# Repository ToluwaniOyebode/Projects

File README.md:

# Projects

## Data, AI and ML portfolio

[Explore three end-to-end ML projects →](ML-Projects/README.md)

| Project | Focus |
| --- | --- |
| [Churn Intelligence](ML-Projects/churn-intelligence/) | Model comparison, calibration and a profit-based retention decision |
| [Demand Forecasting Lab](ML-Projects/demand-forecasting-lab/) | Leakage-safe rolling backtests, promotions and prediction intervals |
| [Ticket Triage NLP](ML-Projects/ticket-triage-nlp/) | Unseen-phrasing evaluation, confidence routing and similar-ticket search |

Each project reproduces from one command, ships its real results and figures, and states its own limitations. Data is synthetic and generated locally.

## Software engineering portfolio

[Explore six complete local applications →](Portfolio-Projects/README.md)

| Project                                      | Focus                                                            |
| -------------------------------------------- | ---------------------------------------------------------------- |
| [Applyboard](Portfolio-Projects/applyboard/) | Job application pipeline, versioned edits and follow-ups         |
| [LedgerLens](Portfolio-Projects/ledgerlens/) | Exact-money expense analytics, budgets and validated CSV imports |
| [Stockroom](Portfolio-Projects/stockroom/)   | Transactional inventory, idempotent reservations and fulfillment |
| [SignalDesk](Portfolio-Projects/signaldesk/) | Local document search with explainable BM25 ranking              |
| [Pitchside](Portfolio-Projects/pitchside/)   | Football event analytics, passing networks and shot maps         |
| [QueueCraft](Portfolio-Projects/queuecraft/) | Persistent background jobs, retries and crash-safe leases        |

Each project includes a working UI, demo data, an API guide, tests and local setup instructions. The collection has 45 domain tests plus HTTP and optional browser acceptance checks. [Validation evidence](Portfolio-Projects/VALIDATION.md) · [Demo and interview guide](Portfolio-Projects/INTERVIEW_GUIDE.md)

## Other projects

- [Project R.O.D.R.I.](Project-R.O.D.R.I./) — ongoing football analysis work.
- [ESP32](ESP32/) · [NodeMCU](NODEMCU/) · [Raspberry Pi](RASPBERRY/) — hardware and embedded projects.
- Stock-market notebooks and datasets in the repository root.

New portfolio applications use fictional/synthetic sample data and were built with AI assistance. Existing work remains separate from the new collection.

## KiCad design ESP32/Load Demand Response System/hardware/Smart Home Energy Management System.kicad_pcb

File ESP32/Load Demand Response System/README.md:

# Load Demand Response System
Generated using KiCad Industrial Setup Script

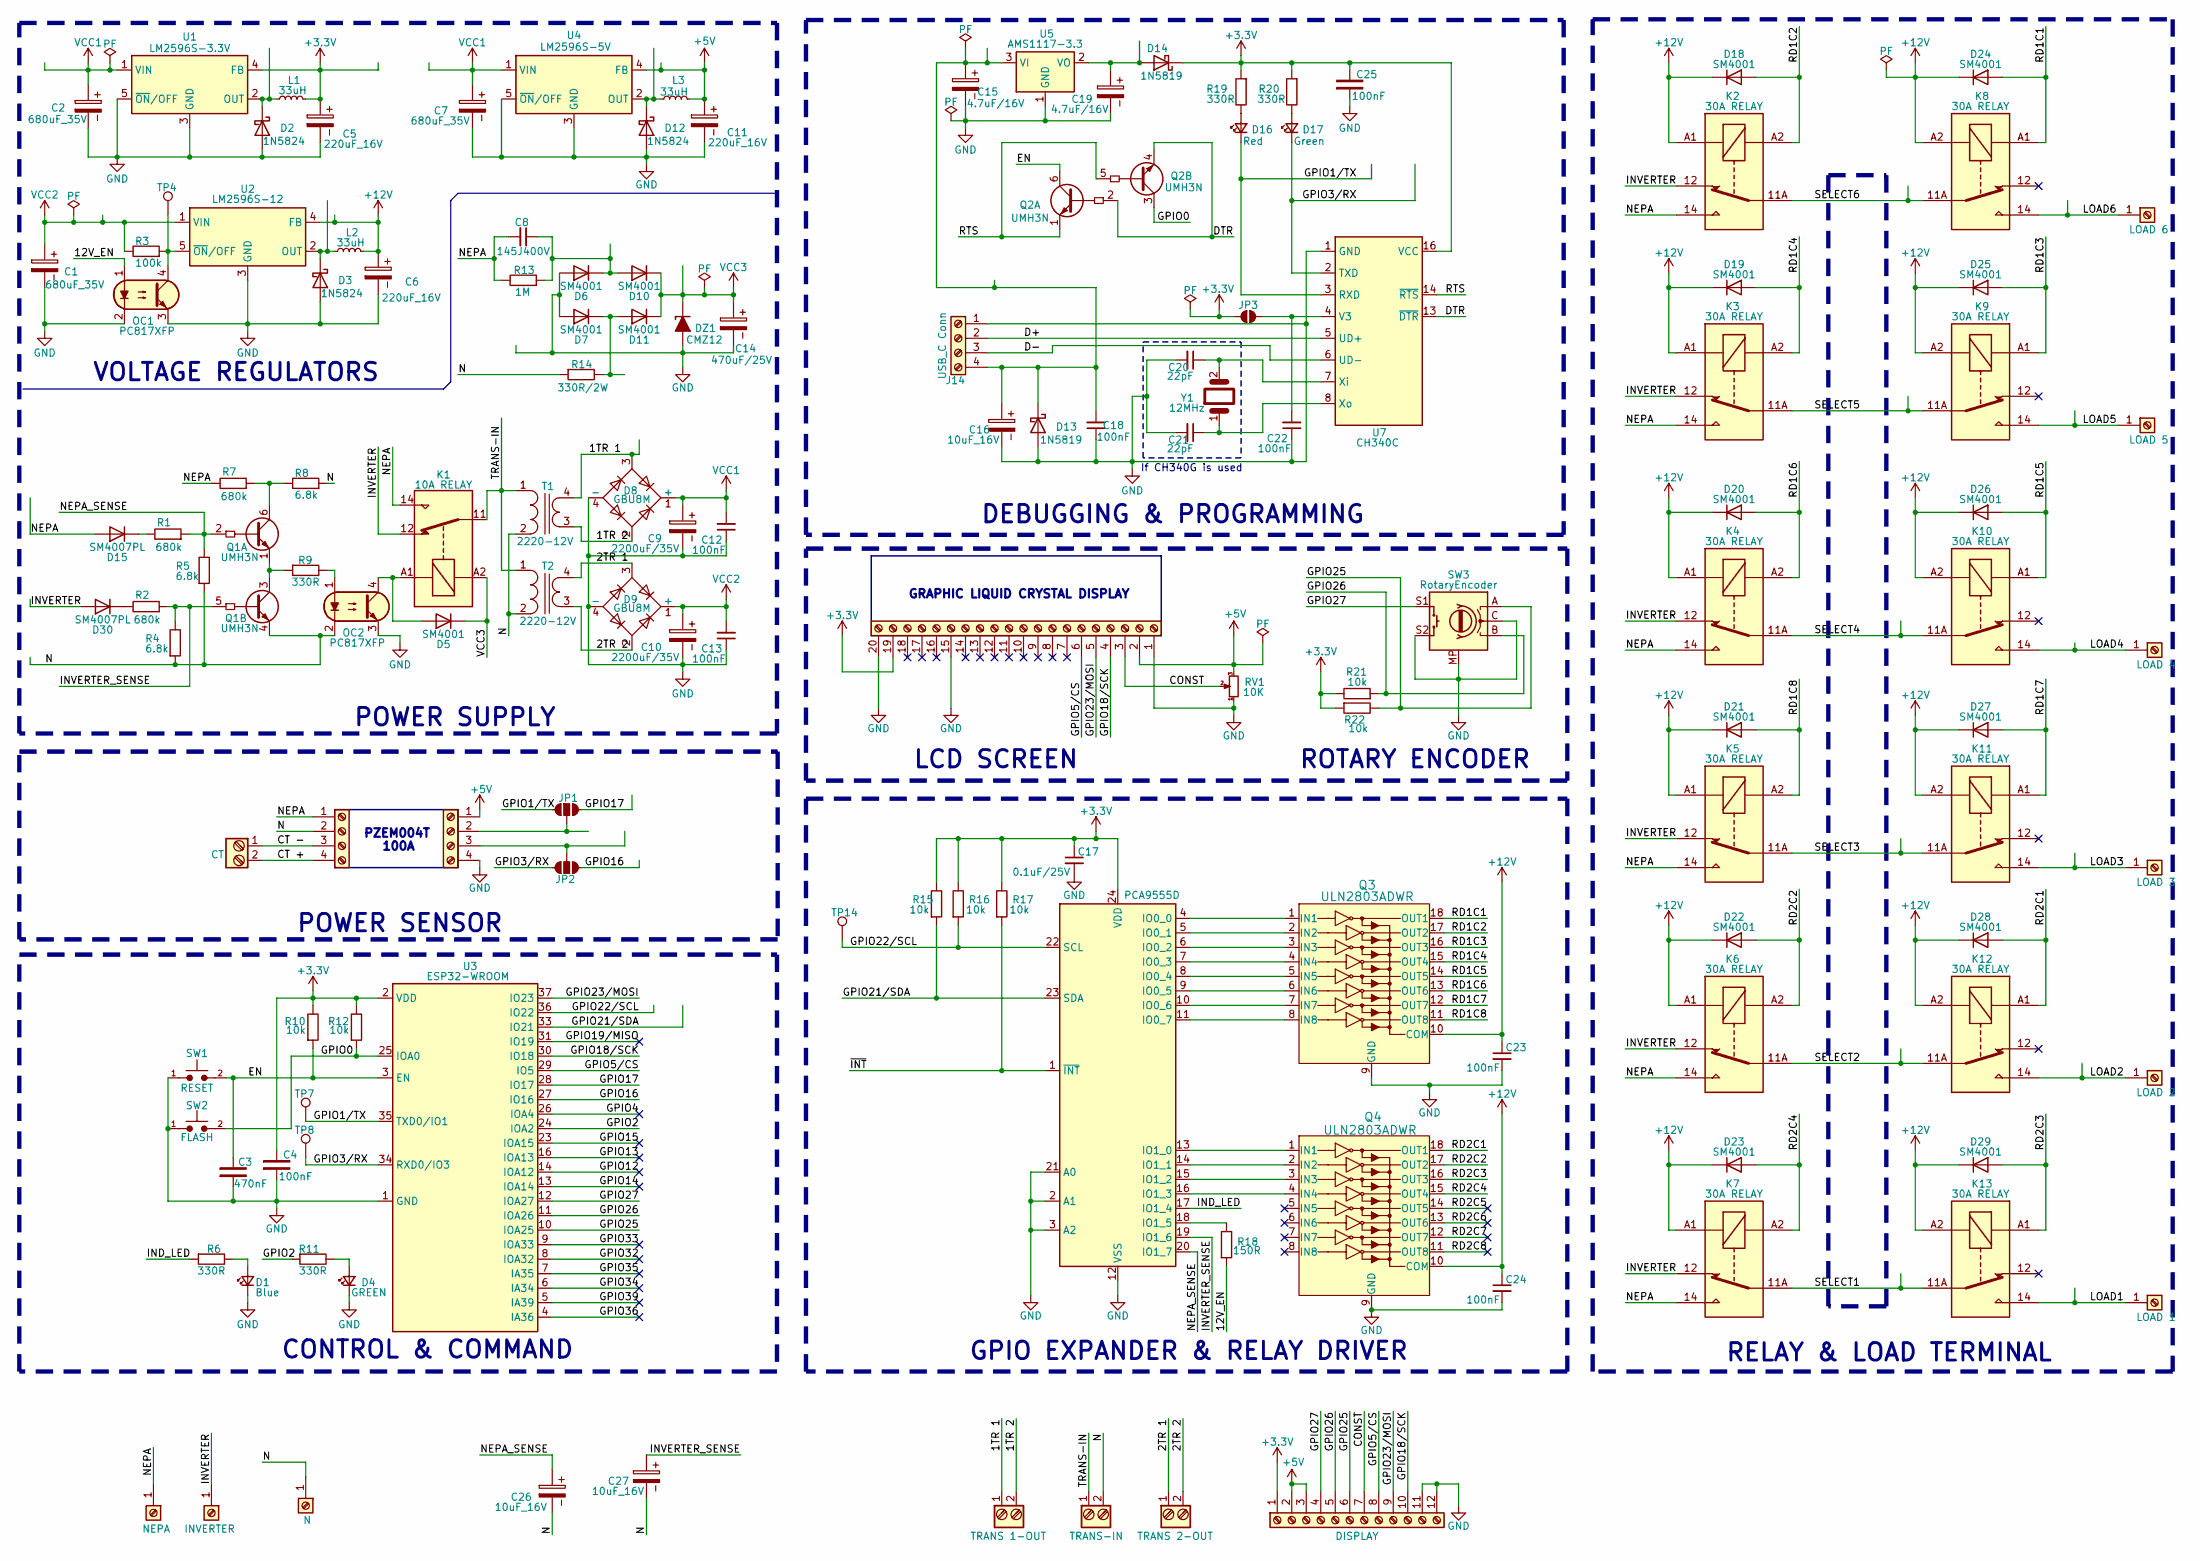
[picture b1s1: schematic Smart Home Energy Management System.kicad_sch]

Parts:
C1, C2, C7: 680uF_35V; CP_Elec_10x12.5
C3: 470nF; C_0805
C4, C12, C13, C18, C22, C25: 100nF; C_0805
C5, C6, C11: 220uF_16V; CP_Elec_6.3x7.7
C8: 145J400V; C_Rect_L19.0mm_W6.0mm_P15.00mm_MKS4
C9, C10: 2200uF/35V; CP_Radial_D18.0mm_P7.50mm
C14: 470uF/25V; CP_Elec_8x11.9
C15: 4.7uF/16V; C_CASE-B-3528-21(mm)
C16, C26, C27: 10uF_16V; C_CASE-B-3528-21(mm)
C17: 0.1uF/25V; C_0805; Voltage 25V; Tolerance 20%
C19: 4.7uF/16V; CP_EIA-3216-18_Kemet-A
C20, C21: 22pF; C_0805
C23, C24: 100nF; C_0805; Voltage 25V; Tolerance 20%
D1: Blue; LED_D3.0mm
D2, D3, D12: 1N5824; D_SMA
D4: GREEN; LED_D3.0mm
D5, D6, D7, D10, D11, D18, D19, D20, D21, D22, D23, D24, D25, D26, D27, D28, D29: SM4001; D_SMA
D8, D9: GBU8M; Diode_Bridge_Vishay_GBU
D13, D14: 1N5819; D_SMA
D15, D30: SM4007PL; D_SMA
D16: Red; LED_D3.0mm
D17: Green; LED_D3.0mm
DZ1: CMZ12; D_SOD-123
J1: NEPA; TestPoint_Plated_Hole_D5.0mm
J2: INVERTER; TestPoint_Plated_Hole_D5.0mm
J3: CT; PinHeader_1x02_P2.54mm_Vertical
J6: PZEM_LOAD; TerminalBlock_MaiXu_MX126-5.0-04P_1x04_P5.00mm
J10: N; TestPoint_Plated_Hole_D5.0mm
J11: PZEM_SIG; PinHeader_1x04_P2.54mm_Vertical
J14: USB_C Conn; PinHeader_1x04_P2.54mm_Vertical
J15: TRANS 1-OUT; TerminalBlock_Phoenix_PT-1,5-2-5.0-H_1x02_P5.00mm_Horizontal
J16: 128X64 GLCD
J17: TRANS-IN; TerminalBlock_Phoenix_PT-1,5-2-5.0-H_1x02_P5.00mm_Horizontal
J18: TRANS 2-OUT; TerminalBlock_Phoenix_PT-1,5-2-5.0-H_1x02_P5.00mm_Horizontal
J19: DISPLAY; PinHeader_1x12_P2.54mm_Vertical
J20: LOAD 6; TestPoint_Plated_Hole_D5.0mm
J21: LOAD 5; TestPoint_Plated_Hole_D5.0mm
J22: LOAD 4; TestPoint_Plated_Hole_D5.0mm
J23: LOAD 3; TestPoint_Plated_Hole_D5.0mm
J24: LOAD 2; TestPoint_Plated_Hole_D5.0mm
J25: LOAD 1; TestPoint_Plated_Hole_D5.0mm
JP1, JP2: SolderJumper-3_P1.3mm_Open_Pad1.0x1.5mm
JP3: SolderJumper-2_P1.3mm_Open_Pad1.0x1.5mm
K1: 10A RELAY; Relay_SPDT_Finder_36.11
K2, K3, K4, K5, K6, K7, K8, K9, K10, K11, K12, K13: 30A RELAY; Relay_SPDT_RAYEX-L90
L1, L2, L3: 33uH; L_12x12mm_H6mm
OC1, OC2: PC817XFP; SOP-4_4.4x2.6mm_P1.27mm
Q1, Q2: UMH3N; SOT-363_SC-70-6
Q3, Q4: ULN2803ADWR; SOIC-18_W7.5mm; MPN ULN2803ADWR; Digi-Key_PN 296-15777-1-ND
R1, R2, R7: 680k; R_0805
R3: 100k; R_0805
R4, R5, R8: 6.8k; R_0805
R6, R9, R11, R19, R20: 330R; R_0805
R10, R12, R15, R16, R17, R21, R22: 10k; R_0805
R13: 1M; R_Axial_DIN0207_L6.3mm_D2.5mm_P7.62mm_Horizontal
R14: 330R/2W; R_Axial_DIN0309_L9.0mm_D3.2mm_P20.32mm_Horizontal
R18: 150R; R_0805
RV1: 10K; Potentiometer_Bourns_3296W_Vertical
SW1: RESET; SW_TS-1088-AR02016
SW2: FLASH; SW_TS-1088-AR02016
SW3: RotaryEncoder
T1, T2: 2220-12V
TP4, TP7, TP8, TP14: TestPoint; TestPoint_Pad_D1.5mm
U1: LM2596S-3.3V; TO-263-5_L10.2-W8.9-P1.70-TL
U2: LM2596S-12; TO-263-5_L10.2-W8.9-P1.70-TL
U3: ESP32-WROOM; ESP32-WROOM-32E
U4: LM2596S-5V; TO-263-5_L10.2-W8.9-P1.70-TL
U5: AMS1117-3.3; SOT-223-3_L6.5-W3.4-P2.30-LS7.0-BR
U6: PCA9555D; SOIC-24W_7.5x15.4mm_P1.27mm
U7: CH340C; SOIC-16_3.9x9.9mm_P1.27mm
Y1: 12MHz; CRYSTAL-SMD_L11.5-W4.8-LS12.7

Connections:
+3.3V: C4.2, C5.1, C17.1, C25.2, D14.1 (K), J16.19, J19.1, JP3.2 (B), L1.2, R10.2, R12.2, R15.2, R16.2, R17.2, R19.1, R20.1, R21.2, R22.1, U1.4 (FB), U3.2 (VDD), U6.24 (VDD), U7.16 (VCC)
+5V: C11.1, J11.1, J16.2, J19.2, J19.3, L3.2, RV1.3, U4.4 (FB)
+12V: C6.1, C23.1, C24.1, D18.1 (K), D19.1 (K), D20.1 (K), D21.1 (K), D22.1 (K), D23.1 (K), D24.1 (K), D25.1 (K), D26.1 (K), D27.1 (K), D28.1 (K), D29.1 (K), K2.A1, K3.A1, K4.A1, K5.A1, K6.A1, K7.A1, K8.A2, K9.A2, K10.A2, K11.A2, K12.A2, K13.A2, L2.2, Q3.10 (COM), Q4.10 (COM), U2.4 (FB)
/1TR 1: D8.3, J15.1, T1.4 (SB)
/1TR 2: D8.2, J15.2, T1.3 (SA)
/2TR 1: D9.3, J18.1, T2.4 (SB)
/2TR 2: D9.2, J18.2, T2.3 (SA)
/12V_EN: OC1.1, R18.1
/CONST: J16.3, J19.7, RV1.2
/CT +: J3.2, J6.4
/CT -: J3.1, J6.3
/D+: J14.2, U7.5 (UD+)
/D-: J14.3, U7.6 (UD-)
/DTR: Q2.2 (B1), Q2.4 (E2), U7.13 (~DTR)
/EN: C3.2, Q2.6 (C1), R10.1, SW1.2, U3.3 (EN)
/GPIO0: Q2.3 (C2), R12.1, SW2.2, U3.25 (IOA0)
/GPIO1/TX: D16.1 (K), JP1.1 (A), TP7.1, U3.35 (TXD0/IO1), U7.3 (RXD)
/GPIO2: R11.1, U3.24 (IOA2)
/GPIO3/RX: D17.1 (K), JP2.3 (C), TP8.1, U3.34 (RXD0/IO3), U7.2 (TXD)
/GPIO4: U3.26 (IOA4)
/GPIO5/CS: J16.6, J19.8, U3.29 (IO5)
/GPIO12: U3.14 (IOA12)
/GPIO13: U3.16 (IOA13)
/GPIO14: U3.13 (IOA14)
/GPIO15: U3.23 (IOA15)
/GPIO16: JP2.1 (A), U3.27 (IO16)
/GPIO17: JP1.3 (C), U3.28 (IO17)
/GPIO18/SCK: J16.4, J19.10, U3.30 (IO18)
/GPIO19/MISO: U3.31 (IO19)
/GPIO21/SDA: R15.1, U3.33 (IO21), U6.23 (SDA)
/GPIO22/SCL: R16.1, TP14.1, U3.36 (IO22), U6.22 (SCL)
/GPIO23/MOSI: J16.5, J19.9, U3.37 (IO23)
/GPIO25: J19.6, R22.2, SW3.A, U3.10 (IOA25)
/GPIO26: J19.5, R21.1, SW3.B, U3.11 (IOA26)
/GPIO27: J19.4, SW3.S1, U3.12 (IOA27)
/GPIO32: U3.8 (IOA32)
/GPIO33: U3.9 (IOA33)
/GPIO34: U3.6 (IA34)
/GPIO35: U3.7 (IA35)
/GPIO36: U3.4 (IA36)
/GPIO39: U3.5 (IA39)
/IND_LED: R6.1, U6.17 (IO1_4)
/INVERTER: D30.2 (A), J2.1, K1.12, K2.12, K3.12, K4.12, K5.12, K6.12, K7.12
/INVERTER_SENSE: C27.1, Q1.5 (B2), R2.1, R4.2, U6.19 (IO1_6)
/LOAD1: J25.1, K13.14
/LOAD2: J24.1, K12.14
/LOAD3: J23.1, K11.14
/LOAD4: J22.1, K10.14
/LOAD5: J21.1, K9.14
/LOAD6: J20.1, K8.14
/N: C26.2, C27.2, J6.2, J10.1, J17.2, OC2.2, Q1.4 (E2), R4.1, R5.1, R8.1, R14.1, T1.2 (AB), T2.2 (AB)
/NEPA: C8.2, D15.2 (A), J1.1, J6.1, K1.14, K2.14, K3.14, K4.14, K5.14, K6.14, K7.14, R7.2, R13.2
/NEPA_SENSE: C26.1, Q1.2 (B1), R1.1, R5.2, U6.20 (IO1_7)
/RD1C1: D24.2 (A), K8.A1, Q3.18 (OUT1)
/RD1C2: D18.2 (A), K2.A2, Q3.17 (OUT2)
/RD1C3: D25.2 (A), K9.A1, Q3.16 (OUT3)
/RD1C4: D19.2 (A), K3.A2, Q3.15 (OUT4)
/RD1C5: D26.2 (A), K10.A1, Q3.14 (OUT5)
/RD1C6: D20.2 (A), K4.A2, Q3.13 (OUT6)
/RD1C7: D27.2 (A), K11.A1, Q3.12 (OUT7)
/RD1C8: D21.2 (A), K5.A2, Q3.11 (OUT8)
/RD2C1: D28.2 (A), K12.A1, Q4.18 (OUT1)
/RD2C2: D22.2 (A), K6.A2, Q4.17 (OUT2)
/RD2C3: D29.2 (A), K13.A1, Q4.16 (OUT3)
/RD2C4: D23.2 (A), K7.A2, Q4.15 (OUT4)
/RD2C5: Q4.14 (OUT5)
/RD2C6: Q4.13 (OUT6)
/RD2C7: Q4.12 (OUT7)
/RD2C8: Q4.11 (OUT8)
/RTS: Q2.1 (E1), Q2.5 (B2), U7.14 (~RTS)
/SELECT1: K7.11A, K7.11B, K13.11A, K13.11B
/SELECT2: K6.11A, K6.11B, K12.11A, K12.11B
/SELECT3: K5.11A, K5.11B, K11.11A, K11.11B
/SELECT4: K4.11A, K4.11B, K10.11A, K10.11B
/SELECT5: K3.11A, K3.11B, K9.11A, K9.11B
/SELECT6: K2.11A, K2.11B, K8.11A, K8.11B
/TRANS-IN: J17.1, K1.11, T1.1 (AA), T2.1 (AA)
/~INT: R17.1, U6.1 (~INT)
GND: C1.2, C2.2, C3.1, C4.1, C5.2, C6.2, C7.2, C9.2, C10.2, C11.2, C12.1, C13.1, C14.2, C15.2, C16.2, C17.2, C18.1, C19.2, C20.2, C21.2, C22.1, C23.2, C24.2, C25.1, D1.1 (K), D2.2 (A), D3.2 (A), D4.1 (K), D6.2 (A), D7.2 (A), D8.4 (-), D9.4 (-), D12.2 (A), D13.2 (A), DZ1.2 (A), J11.4, J14.1, J16.1, J16.15, J16.20, J19.11, J19.12, OC1.2, OC1.3, OC2.3, Q3.9 (GND), Q4.9 (GND), RV1.1, SW1.1, SW2.1, SW3.C, SW3.MP, SW3.S2, U1.3 (GND), U1.5 (~ON/OFF), U1.6 (GND), U2.3 (GND), U2.6 (GND), U3.1 (GND), U3.15 (GND), U3.38 (GND), U3.39 (GND), U4.3 (GND), U4.5 (~ON/OFF), U4.6 (GND), U5.1 (GND), U6.2 (A1), U6.3 (A2), U6.12 (VSS), U6.21 (A0), U7.1 (GND)
unnamed: D1.2 (A), R6.2
unnamed: D2.1 (K), L1.1, U1.2 (OUT)
unnamed: D3.1 (K), L2.1, U2.2 (OUT)
unnamed: D4.2 (A), R11.2
unnamed: D5.2 (A), K1.A1, OC2.4
unnamed: C8.1, D6.1 (K), D10.2 (A), R13.1
unnamed: D7.1 (K), D11.2 (A), R14.2
unnamed: D12.1 (K), L3.1, U4.2 (OUT)
unnamed: C15.1, C16.1, C18.2, D13.1 (K), J14.4, U5.3 (VI)
unnamed: C19.1, D14.2 (A), U5.2 (VO), U5.4 (VO)
unnamed: D15.1 (K), R1.2
unnamed: D16.2 (A), R19.2
unnamed: D17.2 (A), R20.2
unnamed: D30.1 (K), R2.2
unnamed: J11.2, JP1.2 (B)
unnamed: J11.3, JP2.2 (B)
unnamed: C22.2, JP3.1 (A), U7.4 (V3)
unnamed: OC2.1, R9.2
unnamed: Q1.6 (C1), R7.1, R8.2
unnamed: Q1.1 (E1), Q1.3 (C2), R9.1
unnamed: Q3.1 (IN1), U6.4 (IO0_0)
unnamed: Q3.2 (IN2), U6.5 (IO0_1)
unnamed: Q3.3 (IN3), U6.6 (IO0_2)
unnamed: Q3.4 (IN4), U6.7 (IO0_3)
unnamed: Q3.5 (IN5), U6.8 (IO0_4)
unnamed: Q3.6 (IN6), U6.9 (IO0_5)
unnamed: Q3.7 (IN7), U6.10 (IO0_6)
unnamed: Q3.8 (IN8), U6.11 (IO0_7)
unnamed: Q4.1 (IN1), U6.13 (IO1_0)
unnamed: Q4.2 (IN2), U6.14 (IO1_1)
unnamed: Q4.3 (IN3), U6.15 (IO1_2)
unnamed: Q4.4 (IN4), U6.16 (IO1_3)
unnamed: OC1.4, R3.1, TP4.1, U2.5 (~ON/OFF)
unnamed: R18.2, U6.18 (IO1_5)
unnamed: C20.1, U7.7 (Xi), Y1.2
unnamed: C21.1, U7.8 (Xo), Y1.1
VCC1: C2.1, C7.1, C9.1, C12.2, D8.1 (+), U1.1 (VIN), U4.1 (VIN)
VCC2: C1.1, C10.1, C13.2, D9.1 (+), R3.2, U2.1 (VIN)
VCC3: C14.1, D5.1 (K), D10.1 (K), D11.1 (K), DZ1.1 (K), K1.A2

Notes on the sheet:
VOLTAGE REGULATORS
LCD SCREEN
ROTARY ENCODER
POWER SUPPLY
If CH340G is used
DEBUGGING & PROGRAMMING
POWER SENSOR
RELAY & LOAD TERMINAL
CONTROL & COMMAND
PZEM004T
GRAPHIC LIQUID CRYSTAL DISPLAY
100A
GPIO EXPANDER & RELAY DRIVER

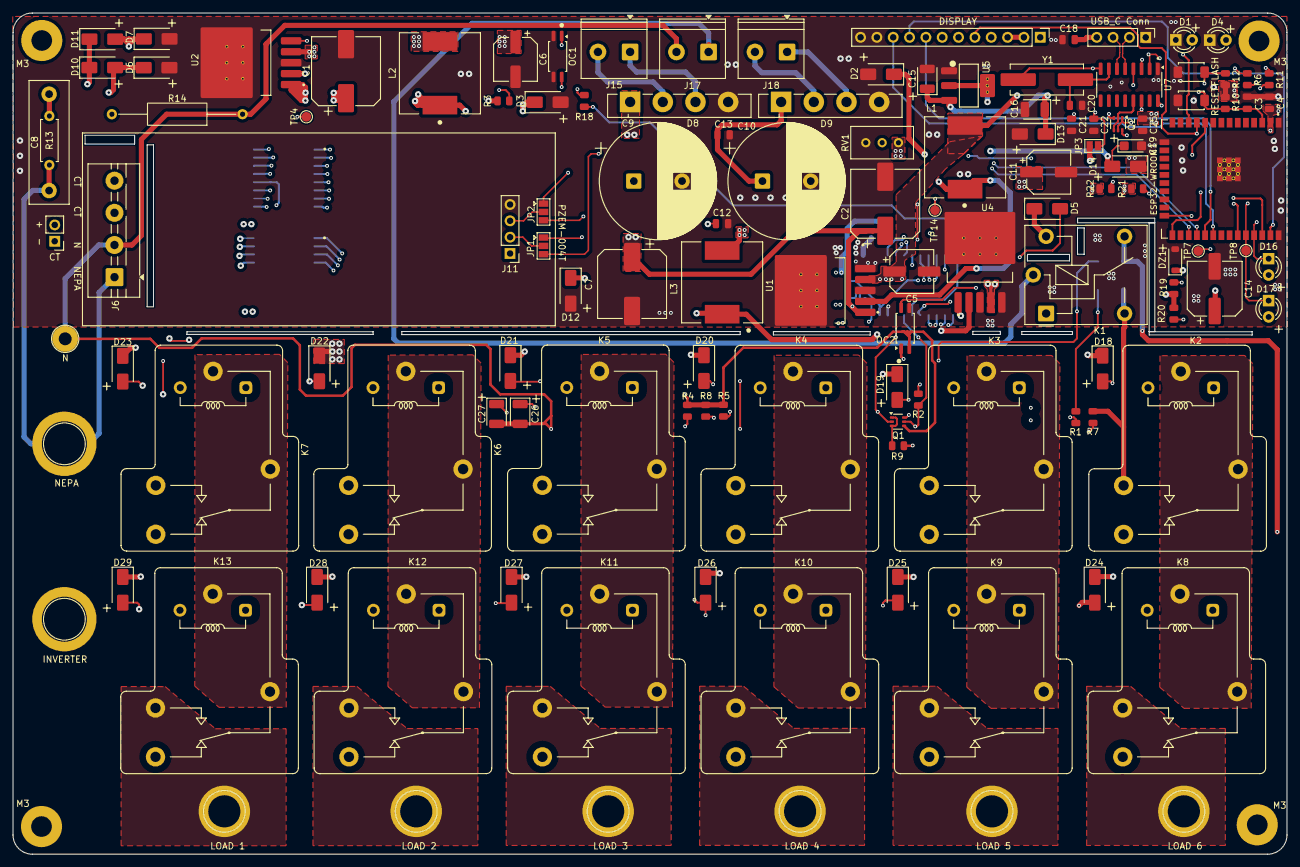
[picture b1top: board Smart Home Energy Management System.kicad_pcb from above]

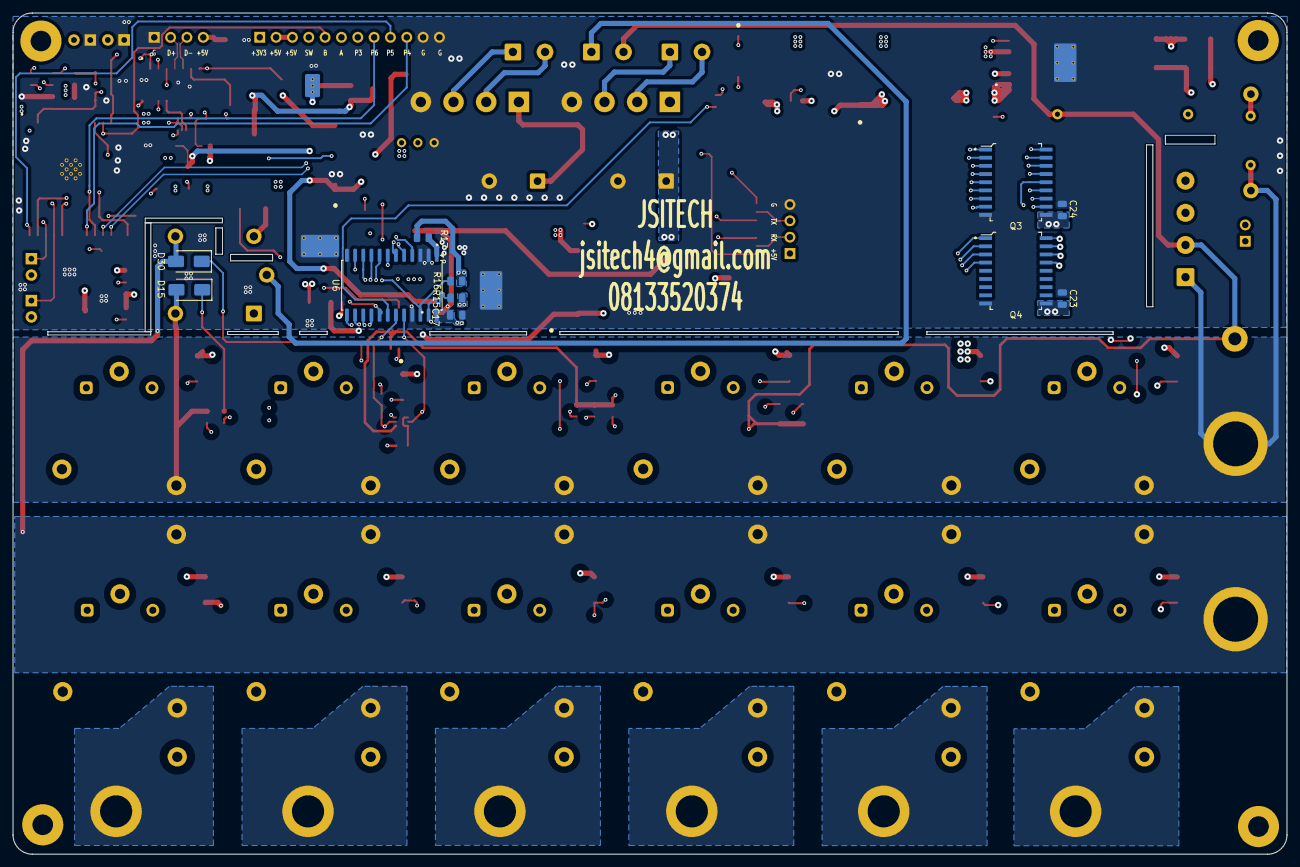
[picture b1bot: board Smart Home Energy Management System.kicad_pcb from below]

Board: 4 copper layers, 198.1 x 130.8 mm, 137 parts (11 on the bottom side), 102 nets.

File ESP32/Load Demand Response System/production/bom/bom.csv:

Designator,Footprint,Quantity,Value,LCSC Part #
"C1, C2, C7",CP_Elec_10x12.5,3,680uF_35V,
"C10, C9",CP_Radial_D18.0mm_P7.50mm,2,2200uF/35V,
"C11, C5, C6",CP_Elec_6.3x7.7,3,220uF_16V,
"C12, C13, C18, C22, C23, C24, C25, C4",C_0805,8,100nF,
C14,CP_Elec_8x11.9,1,470uF/25V,
C15,C_CASE-B-3528-21(mm),1,4.7uF/16V,
"C16, C26, C27",C_CASE-B-3528-21(mm),3,10uF_16V,
C17,C_0805,1,0.1uF/25V,
C19,CP_EIA-3216-18_Kemet-A,1,4.7uF/16V,
"C20, C21",C_0805,2,22pF,
C3,C_0805,1,470nF,
C8,C_Rect_L19.0mm_W6.0mm_P15.00mm_MKS4,1,145J400V,
D1,LED_D3.0mm,1,Blue,
"D10, D11, D18, D19, D20, D21, D22, D23, D24, D25, D26, D27, D28, D29, D5, D6, D7",D_SMA,17,SM4001,
"D12, D2, D3",D_SMA,3,1N5824,
"D13, D14",D_SMA,2,1N5819,
"D15, D30",D_SMA,2,SM4007PL,
D16,LED_D3.0mm,1,Red,
"D17, D4",LED_D3.0mm,2,Green,
"D8, D9",Diode_Bridge_Vishay_GBU,2,GBU8M,
DZ1,D_SOD-123,1,CMZ12,
J1,TestPoint_Plated_Hole_D5.0mm,1,NEPA,
J10,TestPoint_Plated_Hole_D5.0mm,1,N,
J11,PinHeader_1x04_P2.54mm_Vertical,1,PZEM_SIG,
J14,PinHeader_1x04_P2.54mm_Vertical,1,USB_C Conn,
J15,"TerminalBlock_Phoenix_PT-1,5-2-5.0-H_1x02_P5.00mm_Horizontal",1,TRANS 1-OUT,
J17,"TerminalBlock_Phoenix_PT-1,5-2-5.0-H_1x02_P5.00mm_Horizontal",1,TRANS-IN,
J18,"TerminalBlock_Phoenix_PT-1,5-2-5.0-H_1x02_P5.00mm_Horizontal",1,TRANS 2-OUT,
J19,PinHeader_1x12_P2.54mm_Vertical,1,DISPLAY,
J2,TestPoint_Plated_Hole_D5.0mm,1,INVERTER,
J20,TestPoint_Plated_Hole_D5.0mm,1,LOAD 6,
J21,TestPoint_Plated_Hole_D5.0mm,1,LOAD 5,
J22,TestPoint_Plated_Hole_D5.0mm,1,LOAD 4,
J23,TestPoint_Plated_Hole_D5.0mm,1,LOAD 3,
J24,TestPoint_Plated_Hole_D5.0mm,1,LOAD 2,
J25,TestPoint_Plated_Hole_D5.0mm,1,LOAD 1,
J3,PinHeader_1x02_P2.54mm_Vertical,1,CT,
J6,TerminalBlock_MaiXu_MX126-5.0-04P_1x04_P5.00mm,1,PZEM_LOAD,
"JP1, JP2",SolderJumper-3_P1.3mm_Open_Pad1.0x1.5mm,2,~,
JP3,SolderJumper-2_P1.3mm_Open_Pad1.0x1.5mm,1,~,
K1,Relay_SPDT_Finder_36.11,1,10A RELAY,
"K10, K11, K12, K13, K2, K3, K4, K5, K6, K7, K8, K9",Relay_SPDT_RAYEX-L90,12,30A RELAY,
"L1, L2, L3",L_12x12mm_H6mm,3,33uH,
"OC1, OC2",SOP-4_4.4x2.6mm_P1.27mm,2,PC817XFP,
"Q1, Q2",SOT-363_SC-70-6,2,UMH3N,
"Q3, Q4",SOIC-18_W7.5mm,2,ULN2803ADWR,ULN2803ADWR
"R1, R2, R7",R_0805,3,680k,
"R10, R12, R15, R16, R17, R21, R22",R_0805,7,10k,
"R11, R19, R20, R6, R9",R_0805,5,330R,
R13,R_Axial_DIN0207_L6.3mm_D2.5mm_P7.62mm_Horizontal,1,1M,
R14,R_Axial_DIN0309_L9.0mm_D3.2mm_P20.32mm_Horizontal,1,330R/2W,
R18,R_0805,1,150R,
R3,R_0805,1,100k,
"R4, R5, R8",R_0805,3,6.8k,
RV1,Potentiometer_Bourns_3296W_Vertical,1,10K,
SW1,SW_TS-1088-AR02016,1,RESET,
SW2,SW_TS-1088-AR02016,1,FLASH,
"TP14, TP4, TP7, TP8",TestPoint_Pad_D1.5mm,4,TestPoint,
U1,TO-263-5_L10.2-W8.9-P1.70-TL,1,LM2596S-3.3V,
U2,TO-263-5_L10.2-W8.9-P1.70-TL,1,LM2596S-12,
U3,ESP32-WROOM-32E,1,ESP32-WROOM,
U4,TO-263-5_L10.2-W8.9-P1.70-TL,1,LM2596S-5V,
U5,SOT-223-3_L6.5-W3.4-P2.30-LS7.0-BR,1,AMS1117-3.3,
U6,SOIC-24W_7.5x15.4mm_P1.27mm,1,PCA9555D,
U7,SOIC-16_3.9x9.9mm_P1.27mm,1,CH340C,
Y1,CRYSTAL-SMD_L11.5-W4.8-LS12.7,1,12MHz,

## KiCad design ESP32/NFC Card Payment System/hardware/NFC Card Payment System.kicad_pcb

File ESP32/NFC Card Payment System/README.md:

# NFC Card Payment System
Generated using KiCad Industrial Setup Script

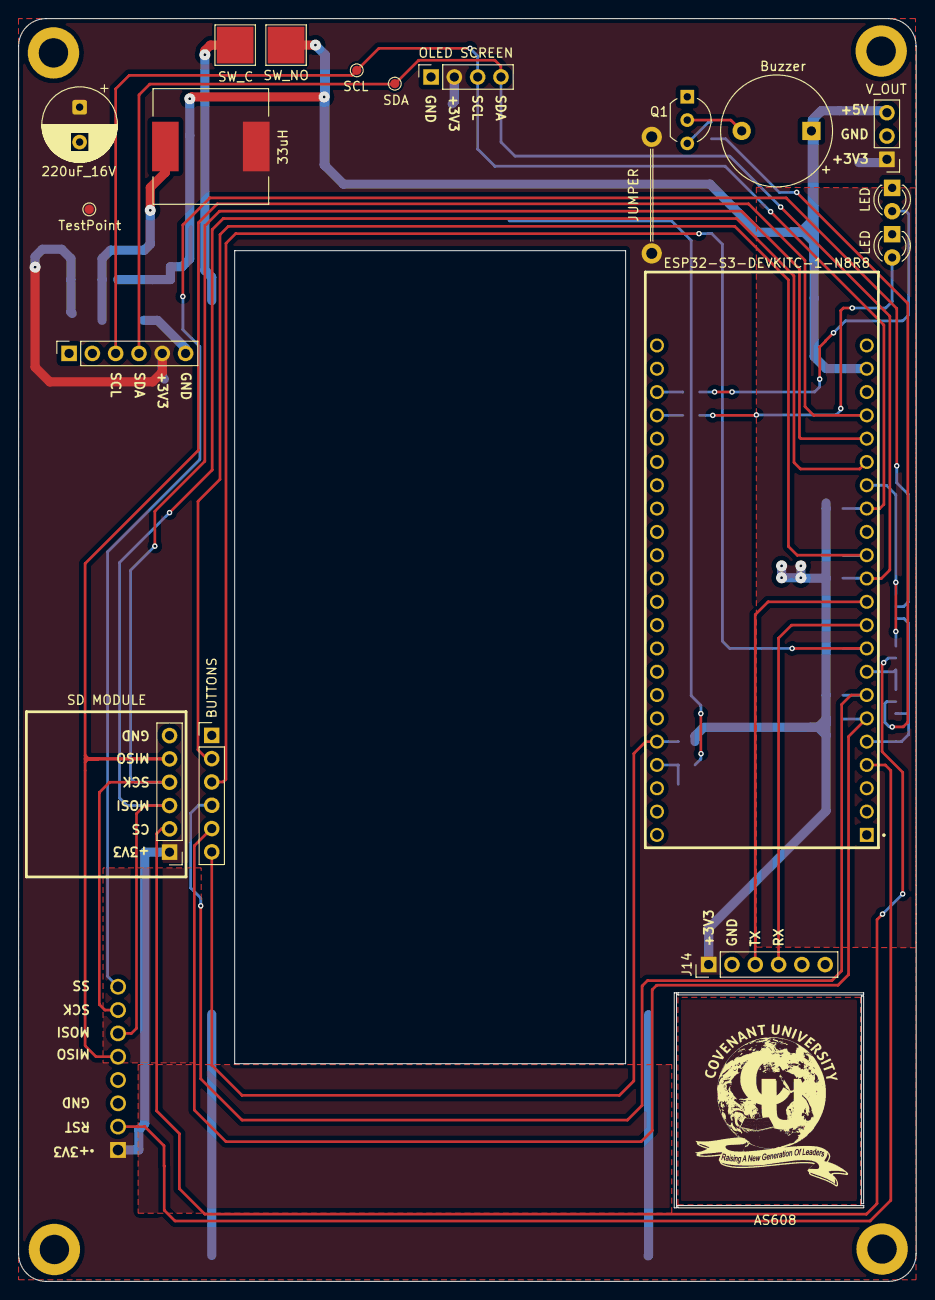
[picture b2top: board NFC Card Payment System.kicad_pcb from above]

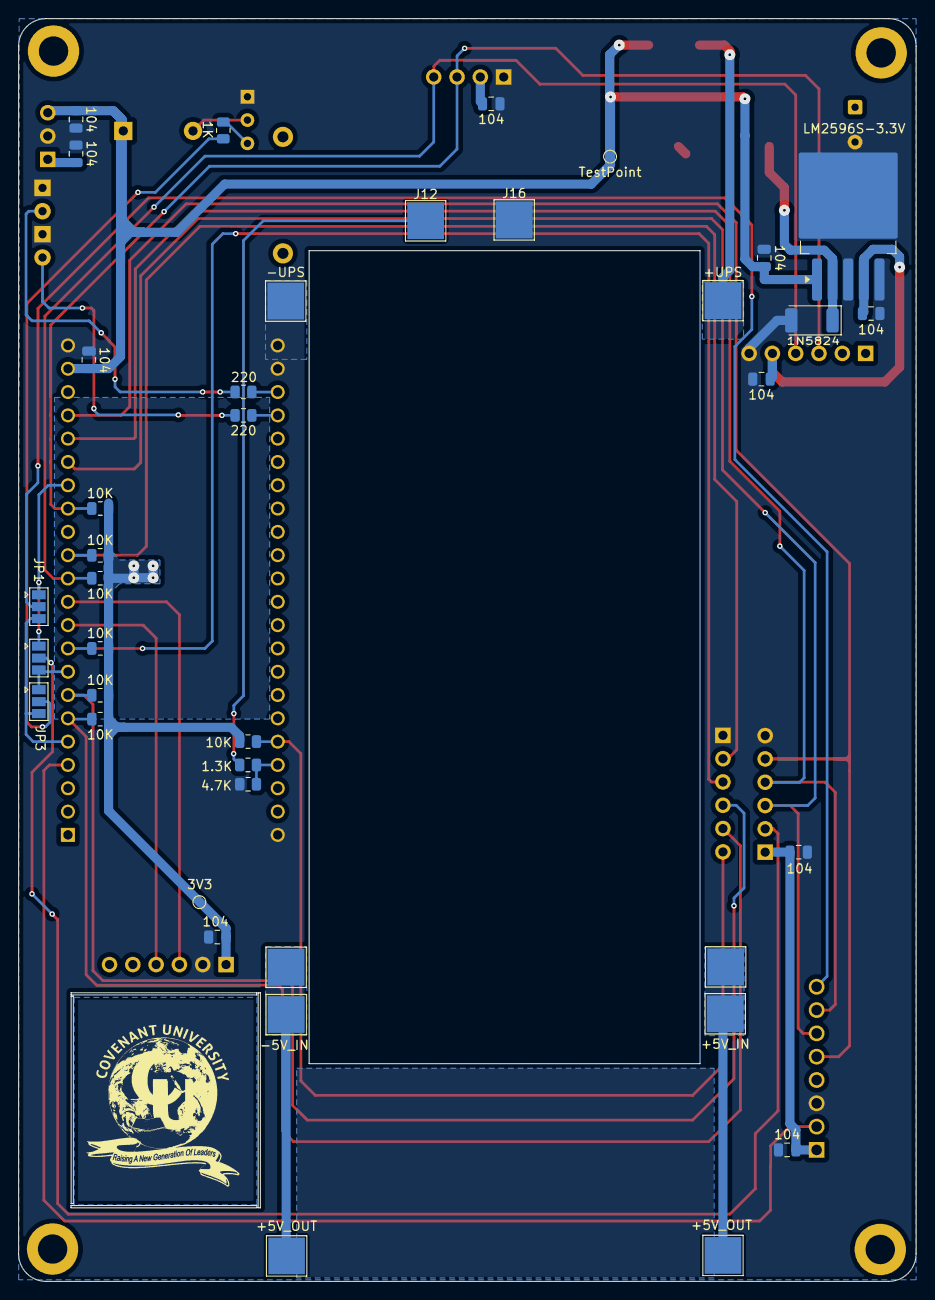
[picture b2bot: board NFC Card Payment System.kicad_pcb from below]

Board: 2 copper layers, 97.8 x 137.6 mm, 58 parts (39 on the bottom side), 34 nets.

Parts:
3.3V2: 3V3; TestPoint_Pad_D1.0mm
3.3V5, 5V1: TestPoint; TestPoint_Pad_D1.0mm
BZ1: Buzzer; Buzzer_12x9.5RM7.6
C1, C2, C3, C4, C5, C7, C8, C9, C10, C11: 104; C_0805_2012Metric
C6: 220uF_16V; CP_Radial_D8.0mm_P3.80mm
D1, D3: LED; LED_D3.0mm
D2: 1N5824; D_2010_5025Metric
J1: RTC; PinSocket_1x06_P2.54mm_Vertical
J2: OLED SCREEN; PinSocket_1x04_P2.54mm_Vertical
J3, J4: +5V_OUT; TestPoint_Pad_4.0x4.0mm
J5, J5#2: +5V_IN; TestPoint_Pad_4.0x4.0mm
J6, J6#2: -5V_IN; TestPoint_Pad_4.0x4.0mm
J9: +UPS; TestPoint_Pad_4.0x4.0mm
J10: -UPS; TestPoint_Pad_4.0x4.0mm
J11: V_OUT; PinHeader_1x03_P2.54mm_Vertical
J12: +BATT; TestPoint_Pad_4.0x4.0mm
J13: BUTTONS; PinHeader_1x06_P2.54mm_Vertical
J14: AS608; PinHeader_1x06_P2.54mm_Vertical
J15: SD MODULE; PinHeader_1x06_P2.54mm_Vertical
J16: -BATT; TestPoint_Pad_4.0x4.0mm
J17: SW_C; TestPoint_Pad_4.0x4.0mm
J18: SW_NO; TestPoint_Pad_4.0x4.0mm
JP1, JP2, JP3: SolderJumper-3_P1.3mm_Open_Pad1.0x1.5mm
L1: 33uH; L_12x12mm_H4.5mm
Q1: 2SC1815; TO-92_Inline_Wide
R1, R2, R7, R8, R9, R10, R11: 10K; R_0805_2012Metric
R3, R4: 220; R_0805_2012Metric
R5: 1.3K; R_0805_2012Metric
R6: 4.7K; R_0805_2012Metric
R12: 1K; R_0805_2012Metric
SCL1: SCL; TestPoint_Pad_D1.0mm
SDA1: SDA; TestPoint_Pad_D1.0mm
U1: ESP32-S3-DEVKITC-1-N8R8; ESP32-S3-DEVKITC
U2: LM2596S-3.3V; TO-263-5_TabPin3
U3: RC522; RC522 RFID

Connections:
+3.3V: 3.3V2.1, 3.3V5.1, C1.1, C2.1, C5.1, C6.1, C8.1, C9.1, C10.1, C11.1, J1.5, J2.2, J11.1, J14.1, J15.1, L1.2, R1.1, R2.1, R7.1, R8.1, R9.1, R10.1, R11.1, U2.4 (FB), U3.1 (VCC)
+5V: 5V1.1, BZ1.1 (+), C3.1, C4.1, C7.1, J11.3, J18.1, U1.J1_21 (5V0), U2.1 (VIN)
/BTN1: J13.6, R11.2, U1.J3_5 (GPIO2)
/BTN2: J13.5, R10.2, U1.J1_6 (GPIO6)
/BTN3: J13.4, R9.2, U1.J1_7 (GPIO7)
/BTN4: J13.3, R8.2, U1.J1_9 (GPIO16)
/BTN5: J13.2, R7.2, U1.J1_13 (GPIO3)
/CS1: JP1.1 (A), JP2.1 (A), U1.J1_16 (GPIO10)
/CS2: JP2.3 (C), JP3.1 (A), U1.J1_8 (GPIO15)
/CS3: JP1.3 (C), JP3.3 (C), U1.J1_5 (GPIO5)
/RC522 RST: U1.J1_4 (GPIO4), U3.2 (RST)
/RC522 SS: JP1.2 (B), U3.8 (SS/SDA/RX)
/RX: J14.3, U1.J1_11 (GPIO18)
/SCL: J1.3, J2.3, R2.2, SCL1.1, U1.J1_15 (GPIO9)
/SD CARD CS: J15.2, JP2.2 (B)
/SDA: J1.4, J2.4, R1.2, SDA1.1, U1.J1_12 (GPIO8)
/SHARED_MISO: J15.5, U1.J1_19 (GPIO13), U3.5 (MISO/SCL/TX)
/SHARED_MOSI: J15.3, U1.J1_17 (GPIO11), U3.6 (MOSI)
/SHARED_SCK: J15.4, U1.J1_18 (GPIO12), U3.7 (SCK)
/TX: J14.4, U1.J1_10 (GPIO17)
GND: C1.2, C2.2, C3.2, C4.2, C5.2, C6.2, C7.2, C8.2, C9.2, C10.2, C11.2, D1.1 (K), D2.2 (A), D3.1 (K), J1.6, J2.1, J10.1, J11.2, J13.1, J14.2, J15.6, J16.1, Q1.1 (E), R6.2, U1.J1_22 (GND3), U1.J3_1 (GND), U1.J3_21 (GND1), U1.J3_22 (GND2), U2.3 (GND), U2.5 (~ON/OFF), U3.3 (GND)
unnamed: BZ1.2 (-), Q1.2 (C)
unnamed: D1.2 (A), R3.1
unnamed: D2.1 (K), L1.1, U2.2 (OUT)
unnamed: D3.2 (A), R4.1
unnamed: J3.1, J5.1, J5#2.1
unnamed: J4.1, J6.1, J6#2.1
unnamed: J12.1, R5.1
unnamed: J9.1, J17.1
unnamed: JP3.2 (B), R12.1
unnamed: Q1.3 (B), R12.2
unnamed: R5.2, R6.1, U1.J3_4 (GPIO1)
unnamed: R4.2, U1.J3_19 (USB_D+/GPIO20)
unnamed: R3.2, U1.J3_20 (USB_D-/GPIO19)
